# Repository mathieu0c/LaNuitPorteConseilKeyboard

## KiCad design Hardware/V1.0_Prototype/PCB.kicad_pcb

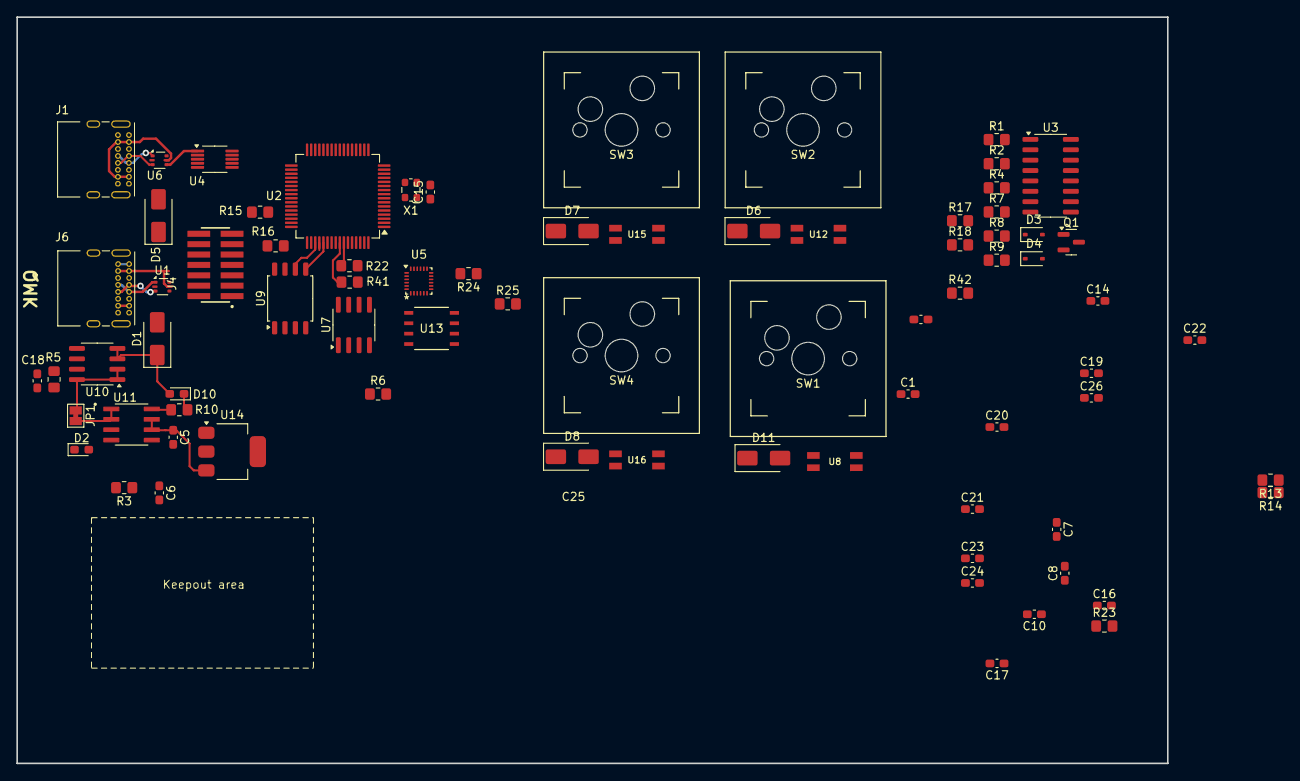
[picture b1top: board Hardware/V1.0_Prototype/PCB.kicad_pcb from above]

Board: 2 copper layers, 140.7 x 91.3 mm, 78 parts (0 on the bottom side), 72 nets.

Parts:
C1, C7, C8, C10, C14, C15, C16, C17, C20, C21, C22, C23, C24, C25: 100nF; C_0603_1608Metric_Pad1.08x0.95mm_HandSolder
C5, C6, C18: 4.7uF; C_0603_1608Metric_Pad1.08x0.95mm_HandSolder
C19, C26: 1µF; C_0603_1608Metric_Pad1.08x0.95mm_HandSolder
D1, D5: SS24; D_SMA
D2, D10: LED; LED_0603_1608Metric_Pad1.05x0.95mm_HandSolder
D3: Z3.3V; D_SOD-323
D4: BAS16HT1G; D_SOD-323
D6, D7, D8, D11: SR360; D_SMA
DS2: OLED-PCB_MOUNT_128_64_30P_Pins; SSD1306_OLED_0.96_PCB
J1, J6: USB_C_Receptacle; USB_C_Receptacle_GCT_USB4085
J4: FTSH-107-01-L-DV-K-P-TR; SAMTEC_FTSH-107-01-L-DV-K-P-TR
JP1: SolderJumper_2_Bridged; SolderJumper-2_P1.3mm_Bridged_Pad1.0x1.5mm
Q1: NMOS; SOT-23
R1: 1k; R_0805_2012Metric_Pad1.20x1.40mm_HandSolder
R2: 100; R_0805_2012Metric_Pad1.20x1.40mm_HandSolder
R3, R5, R10: 330; R_0805_2012Metric_Pad1.20x1.40mm_HandSolder
R4: 18; R_0805_2012Metric_Pad1.20x1.40mm_HandSolder
R6, R9, R23, R24, R25: 10k; R_0805_2012Metric_Pad1.20x1.40mm_HandSolder
R7, R8: 100k; R_0805_2012Metric_Pad1.20x1.40mm_HandSolder
R13, R14, R15, R16, R17, R18: 0; R_0805_2012Metric_Pad1.20x1.40mm_HandSolder
R22, R41, R42: 4.7k; R_0805_2012Metric_Pad1.20x1.40mm_HandSolder
SW1, SW2, SW3, SW4: SW_HotSwap; Hotswap_1U
U1, U6: USBLC6-2P6; SOT-666
U2: STM32F303RETx; LQFP-64_10x10mm_P0.5mm
U3: MC1413BD; SOIC-16_3.9x9.9mm_P1.27mm
U4: CH340E; MSOP-10_3x3mm_P0.5mm
U5: MPU-9250; InvenSense_QFN-24_3x3mm_P0.4mm
U7: DS3231Z; SOIC-8_3.9x4.9mm_P1.27mm
U8, U12, U15, U16: SK6812MINI-E
U9: W25Q128JVS; SOIC-8_5.3x5.3mm_P1.27mm
U10: ACS712xLCTR-05B; SOIC-8_3.9x4.9mm_P1.27mm
U11: ST890
U13: HIH6130-021-001; IC8_HIH6130-021-001_HNW
U14: AMS1117-3.3; SOT-223-3_TabPin2
X1: ECS-2520MV-250-DN-TR; Oscillator_SMD_ECS_2520MV-xxx-xx-4Pin_2.5x2.0mm

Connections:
/EEPROM/+3.3V: C17.2, U9.7 (~HOLD/~RESET/IO_{3})
/EEPROM/CLK: U2.51 (SPI3_SCK), U9.6 (CLK)
/EEPROM/GND: C17.1, U9.4 (GND)
/EEPROM/MISO: U2.52 (SPI3_MISO), U9.2 (DO/IO_{1})
/EEPROM/MOSI: U2.53 (SPI3_MOSI), U9.5 (DI/IO_{0})
/IMU/+3.3V: C6.1, C7.1, C8.1, C10.1, C14.1, C15.1, C21.1, C22.1, C23.1, C24.1, C25.1, D2.2 (A), DS2.6 (VBAT), DS2.9 (VDD), DS2.11 (BS1), DS2.28 (VCC), R24.1, U2.1 (VBAT), U2.13 (VDDA), U2.19 (VDD), U2.32 (VDD), U2.48 (VDD), U2.64 (VDD), U5.8 (VDDIO), U5.13 (VDD), U5.22 (~CS), U13.8 (Vdd), U14.2 (VO), X1.1 (Tri-State), X1.4 (VDD)
/IMU/SCL: R22.2, U2.58 (I2C1_SCL), U5.23 (SCL/SCLK), U7.8 (SCL), U13.3 (SCL)
/IMU/SDA: R41.2, U2.57 (I2C3_SDA), U5.24 (SDA/MOSI), U7.7 (SDA), U13.4 (SDA)
/Key_1U2/Led_Output: U15.P$4 (DOUT), U16.P$3 (DIN)
/Key_1U2/Row_Input: D7.1 (K), D8.1 (K)
/Key_1U/Led_Output: U8.P$4 (DOUT), U12.P$3 (DIN)
/Key_1U/Row_Input: D6.1 (K), D11.1 (K)
/MCU/NRST: J4.12, U2.7 (NRST)
/MCU/RX: U2.43 (PA10), U4.8 (TXD)
/MCU/SWC: J4.06, R16.2
/MCU/SWD: J4.04, R15.2
/MCU/TX: U2.42 (PA9), U4.9 (RXD)
/MCU/USB+: R14.2, U1.4 (I/O2)
/MCU/USB-: R13.2, U1.6 (I/O1)
/MCU/VCC_MCU: R22.1, R41.1
/Multimeter/+5V: C5.1, U11.6 (OUT), U11.7 (OUT), U14.3 (VI)
/Multimeter/ADC_OUT: D3.1 (K), D4.1 (K), Q1.3 (S), R1.2, R2.2, R4.1, R7.2, R9.2
/RTC/+3.3V: C20.2, U7.2 (VCC), U7.6 (VBAT)
/RTC/GND: C20.1, U7.5 (GND)
/Supply/+5V: D1.1 (K), D5.1 (K), D10.2 (A), U10.3 (IP-), U10.4 (IP-)
/Supply/GND: C18.2, R6.1, U10.5 (GND), U11.3 (~ON), U11.4 (GND)
/UART_Slot/DATA+: U4.1 (UD+), U6.4 (I/O2)
/UART_Slot/DATA-: U4.2 (UD-), U6.6 (I/O1)
/UART_Slot/GND: C1.2, J1.A1 (GND), J1.A12 (GND), J1.B1 (GND), J1.B12 (GND), U4.3 (GND), U6.2 (GND)
/UART_Slot/VBus: D5.2 (A), J1.A4 (VBUS), J1.A9 (VBUS), J1.B4 (VBUS), J1.B9 (VBUS), U6.5 (VBUS)
/USB_Slot/VBus: D1.2 (A), J6.A4 (VBUS), J6.A9 (VBUS), J6.B4 (VBUS), J6.B9 (VBUS), U1.5 (VBUS)
GND: C7.2, C8.2, C10.2, C14.2, C15.2, C16.2, C21.2, C22.2, C23.2, C24.2, C25.2, D3.2 (A), DS2.10 (BS0), DS2.12 (BS2), DS2.13 (~CS), J4.05, J4.07, J4.11, J6.A1 (GND), J6.A12 (GND), J6.B1 (GND), J6.B12 (GND), R17.1, R23.2, R25.1, U1.2 (GND), U2.12 (VSSA), U2.18 (VSS), U2.31 (VSS), U2.47 (VSS), U2.63 (VSS), U3.5 (I5), U3.6 (I6), U3.7 (I7), U3.8 (GND), U3.9 (COM), U5.18 (GND), U5.20 (RESV_GND), U13.2 (Vss), X1.2 (GND)
unnamed: D2.1 (K), R3.2
unnamed: D4.2 (A), R8.2
unnamed: D6.2 (A), SW2.2
unnamed: D7.2 (A), SW3.2
unnamed: D8.2 (A), SW4.2
unnamed: D10.1 (K), R10.2
unnamed: D11.2 (A), SW1.2
unnamed: C26.1, DS2.5 (C1N)
unnamed: C26.2, DS2.4 (C1P)
unnamed: C19.2, DS2.2 (C2N)
unnamed: C19.1, DS2.3 (C2P)
unnamed: DS2.1 (GND), DS2.30 (GND)
unnamed: J1.A6 (D+), J1.B6 (D+), U6.3 (I/O2)
unnamed: J1.A7 (D-), J1.B7 (D-), U6.1 (I/O1)
unnamed: J6.A6 (D+), J6.B6 (D+), U1.3 (I/O2)
unnamed: J6.A7 (D-), J6.B7 (D-), U1.1 (I/O1)
unnamed: JP1.1 (A), U10.1 (IP+), U10.2 (IP+), U10.8 (VCC)
unnamed: JP1.2 (B), U11.1 (IN), U11.2 (IN)
unnamed: Q1.1 (D), R4.2
unnamed: Q1.2 (G), R8.1
unnamed: R17.2, U2.60 (BOOT0)
unnamed: R13.1, U2.44 (USB_DM)
unnamed: R14.1, U2.45 (USB_DP)
unnamed: R15.1, U2.46 (SYS_JTMS-SWDIO)
unnamed: R16.1, U2.49 (SYS_JTCK-SWCLK)
unnamed: R42.1, U2.62 (PB9)
unnamed: R18.2, U2.5 (PF0)
unnamed: R2.1, U3.16 (O1)
unnamed: R1.1, U3.15 (O2)
unnamed: R9.1, U3.14 (O3)
unnamed: R7.1, U3.13 (O4)
unnamed: C1.1, U4.10 (V3)
unnamed: R24.2, R25.2, U5.9 (AD0/MISO)
unnamed: R23.1, U5.11 (FSYNC)
unnamed: C16.1, U5.10 (REGOUT)
unnamed: C18.1, R5.1, U10.7 (VIOUT)
unnamed: R6.2, U11.5 (SET)
unnamed: R10.1, U11.8 (~FAULT)
unnamed: C5.2, C6.2, R3.1, U14.1 (GND)
unnamed: R18.1, X1.3 (OUT)

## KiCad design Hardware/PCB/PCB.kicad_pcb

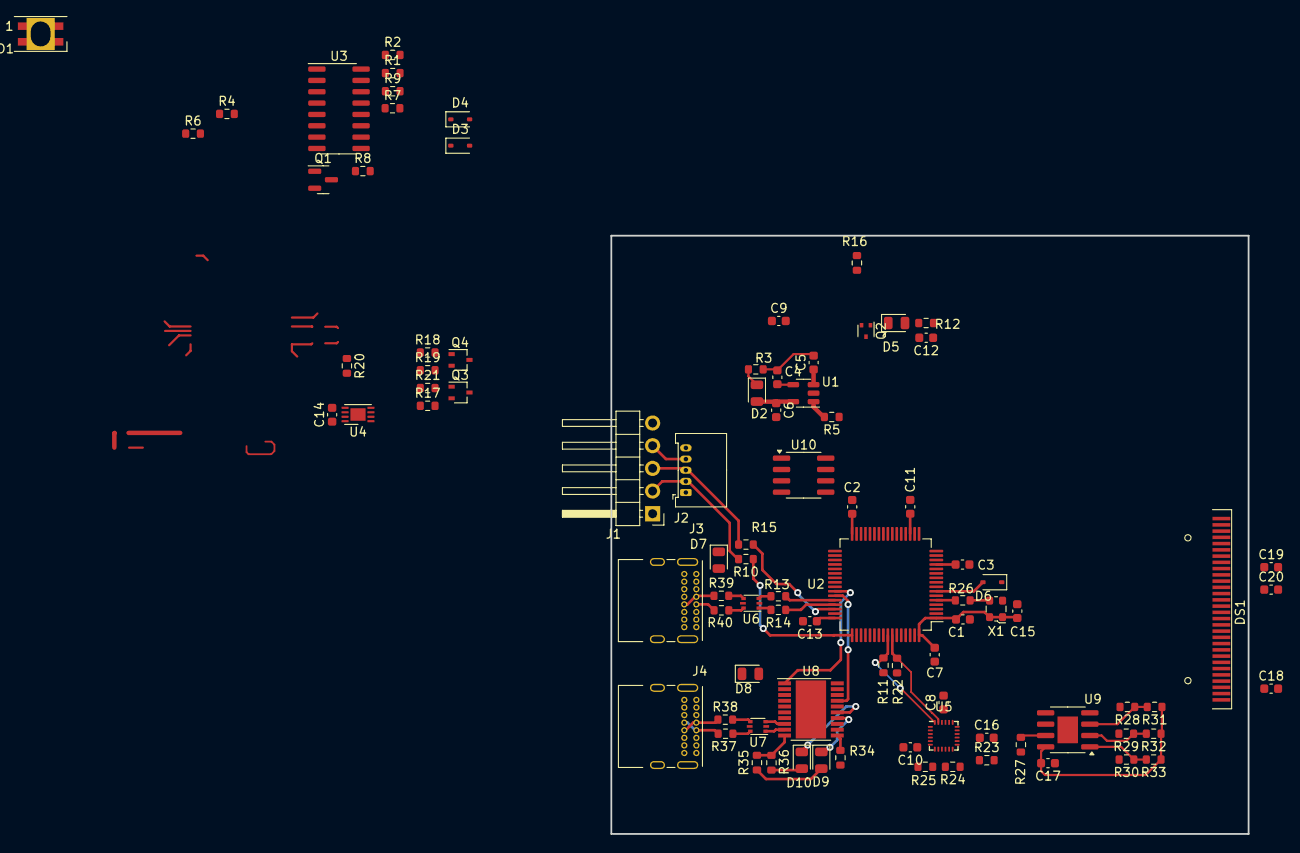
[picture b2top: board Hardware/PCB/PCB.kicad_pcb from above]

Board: 2 copper layers, 71.4 x 67.0 mm, 92 parts (1 on the bottom side), 69 nets.

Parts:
C1, C2, C3, C4, C7, C8, C9, C10, C11, C12, C13, C14, C15, C16, C17: 100nF; C_0603_1608Metric
C5, C6, C18: 4.7uF; C_0603_1608Metric
C19, C20: 1µF; C_0603_1608Metric
D1: SK6812MINI-E; LED_SK6812MINI_PLCC4_3.5x3.5mm_P1.75mm
D2, D5, D9, D10: LED; LED_0805_2012Metric
D3: Z3.3V; D_SOD-323
D4, D6: BAS16HT1G; D_SOD-323
D7, D8: D; D_0805_2012Metric
D11: SR360; D_SMA
DS1: OLED-128O064D
J1: Pin_Header; PinHeader_1x05_P2.54mm_Horizontal
J2: 53048-0510; Molex_PicoBlade_53048-0510_1x05_P1.25mm_Horizontal
J3, J4: USB_C_Receptacle_USB2.0_16P; USB_C_Receptacle_GCT_USB4085
Q1: NMOS; SOT-23
Q2: DMN33D8LT-7; SOT-523
Q3, Q4: PJC138K_R1_00001; SOT-323_SC-70
R1: 1k; R_0603_1608Metric
R2: 100; R_0603_1608Metric
R3, R5, R12, R35, R36: 270; R_0603_1608Metric
R4: 18; R_0603_1608Metric
R6, R10, R13, R14, R15: 0; R_0603_1608Metric
R7, R8, R16: 100k; R_0603_1608Metric
R9, R17, R18, R19, R21, R23, R24, R25, R27, R28, R29, R30, R31, R32, R33, R34: 10k; R_0603_1608Metric
R11, R22: 4.7k; R_0603_1608Metric
R20: 220; R_0603_1608Metric
R26: 10; R_0603_1608Metric
R37, R38, R39, R40: 22; R_0603_1608Metric
SW1: SW_HotSwap; Hotswap_1U
U1: LP2985-3.3; SOT-23-5
U2: STM32F303RETx; LQFP-64_10x10mm_P0.5mm
U3: MC1413BD; SOIC-16_3.9x9.9mm_P1.27mm
U4: MCP98243; DFN-8-1EP_3x2mm_P0.5mm_EP1.7x1.4mm
U5: MPU-9250; InvenSense_QFN-24_3x3mm_P0.4mm
U6, U7: USBLC6-2P6; SOT-666
U8: FT231XQ; HTSSOP-20-1EP_4.4x6.5mm_P0.65mm_EP3.4x6.5mm
U9: 24LC64; SOIC-8-1EP_3.9x4.9mm_P1.27mm_EP2.29x3mm
U10: ACS712xLCTR-05B; SOIC-8_3.9x4.9mm_P1.27mm
X1: ECS-2520MV-250-DN-TR; Oscillator_SMD_ECS_2520MV-xxx-xx-4Pin_2.5x2.0mm

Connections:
/EEPROM/+3.3V: C17.2, R31.1, R32.1, R33.1, U9.8 (VCC)
/EEPROM/GND: C17.1, R27.2, R28.2, R29.2, R30.2, U9.4 (GND)
/IMU/+3.3V: C1.1, C2.1, C3.1, C6.1, C7.1, C8.1, C10.1, C11.1, C13.1, C14.1, C15.1, D2.2 (A), Q3.2 (G), Q4.2 (G), R17.2, R21.2, R24.1, U1.5 (VOUT), U2.1 (VBAT), U2.13 (VDDA), U2.19 (VDD), U2.32 (VDD), U2.48 (VDD), U2.64 (VDD), U4.8 (V_{DD}), U5.8 (VDDIO), U5.13 (VDD), U5.22 (~CS), X1.1 (Tri-State), X1.4 (VDD)
/IMU/SCL: Q3.1 (D), R21.1, R22.2, U2.58 (PB6), U4.2 (SCL), U5.23 (SCL/SCLK)
/IMU/SDA: Q4.1 (D), R11.2, R17.1, U2.57 (PB5), U4.1 (SDA), U5.24 (SDA/MOSI)
/MCU/NRST: C9.1, D6.2 (A), U2.7 (NRST)
/MCU/RX: U2.43 (PA10), U8.17 (TXD)
/MCU/SWC: J1.2, J2.2, R10.2
/MCU/SWD: J1.3, J2.3, Q2.2 (G), R15.2, R16.1
/MCU/TX: U2.42 (PA9), U8.1 (RXD)
/MCU/USB+: R13.2, U6.3 (I/O2)
/MCU/USB-: R14.2, U6.1 (I/O1)
/MCU/VCC_MCU: R11.1, R22.1
/Multimeter/+5V: R18.2, R19.2, U10.3 (IP-), U10.4 (IP-)
/Multimeter/ADC_OUT: D3.1 (K), D4.1 (K), Q1.3 (S), R1.2, R2.2, R4.1, R7.2, R9.2
/OLED/LevelShifter/SCL_HL: Q3.3 (S), R18.1
/OLED/LevelShifter/SDA_HL: Q4.3 (S), R19.1
/Programming/+5V_OUT: C12.1, D7.1 (K), D8.1 (K), J1.4, J2.4, R12.1
/Supply/GND: C4.2, C5.2, C6.2, C18.2, R3.1, U1.2 (GND), U10.5 (GND)
/UART_Slot/+3.3V: R34.1, R35.1, R36.1, U8.10 (3V3OUT)
/UART_Slot/VBus: D8.2 (A), J4.A4 (VBUS), J4.A9 (VBUS), J4.B4 (VBUS), J4.B9 (VBUS), U7.5 (VBUS), U8.12 (VCC), U8.20 (VCCIO)
/USB_Slot/VBus: D7.2 (A), J3.A4 (VBUS), J3.A9 (VBUS), J3.B4 (VBUS), J3.B9 (VBUS), U6.5 (VBUS)
GND: C1.2, C2.2, C3.2, C7.2, C8.2, C9.2, C10.2, C11.2, C12.2, C13.2, C14.2, C15.2, C16.2, D3.2 (A), J1.5, J2.5, J3.A1 (GND), J3.A12 (GND), J3.B1 (GND), J3.B12 (GND), J3.S1 (SHIELD), J4.A1 (GND), J4.A12 (GND), J4.B1 (GND), J4.B12 (GND), J4.S1 (SHIELD), Q2.3 (S), R6.1, R16.2, R23.2, R25.1, U2.12 (VSSA), U2.18 (VSS), U2.31 (VSS), U2.47 (VSS), U2.63 (VSS), U3.5 (I5), U3.6 (I6), U3.7 (I7), U3.8 (GND), U3.9 (COM), U4.4 (GND), U4.5 (A2), U4.6 (A1), U4.7 (A0), U4.9 (EP/GND), U5.18 (GND), U5.20 (RESV_GND), U7.2 (GND), U8.3 (GND), U8.13 (GND), U8.21 (GND), X1.2 (GND)
unnamed: D2.1 (K), R3.2
unnamed: D4.2 (A), R8.2
unnamed: D5.2 (A), R12.2
unnamed: D5.1 (K), Q2.1 (D)
unnamed: D6.1 (K), J1.1, J2.1
unnamed: D9.2 (A), R35.2
unnamed: D9.1 (K), U8.14 (CBUS1)
unnamed: D10.2 (A), R36.2
unnamed: D10.1 (K), U8.15 (CBUS0)
unnamed: D11.2 (A), SW1.2
unnamed: DS1.1 (GND), DS1.30 (GND)
unnamed: J3.A6 (D+), J3.B6 (D+), R39.1
unnamed: J3.A7 (D-), J3.B7 (D-), R40.1
unnamed: J4.A6 (D+), J4.B6 (D+), R38.1
unnamed: J4.A7 (D-), J4.B7 (D-), R37.1
unnamed: Q1.1 (D), R4.2
unnamed: Q1.2 (G), R8.1
unnamed: R37.2, U7.6 (I/O1)
unnamed: R38.2, U7.4 (I/O2)
unnamed: R39.2, U6.4 (I/O2)
unnamed: R40.2, U6.6 (I/O1)
unnamed: C4.1, U1.4 (BP)
unnamed: C5.1, U1.1 (VIN), U1.3 (ON/~OFF), U10.1 (IP+), U10.2 (IP+), U10.8 (VCC)
unnamed: R6.2, U2.60 (BOOT0)
unnamed: R13.1, U2.44 (PA11)
unnamed: R14.1, U2.45 (PA12)
unnamed: R15.1, U2.46 (PA13)
unnamed: R10.1, U2.49 (PA14)
unnamed: R20.1, U2.62 (PB9)
unnamed: R26.2, U2.5 (PF0)
unnamed: R2.1, U3.16 (O1)
unnamed: R1.1, U3.15 (O2)
unnamed: R9.1, U3.14 (O3)
unnamed: R7.1, U3.13 (O4)
unnamed: R24.2, R25.2, U5.9 (AD0/MISO)
unnamed: R23.1, U5.11 (FSYNC)
unnamed: C16.1, U5.10 (REGOUT)
unnamed: U7.1 (I/O1), U8.9 (USBDM)
unnamed: U7.3 (I/O2), U8.8 (USBDP)
unnamed: R34.2, U8.11 (~RESET)
unnamed: R30.1, R33.2, U9.1 (A0)
unnamed: R29.1, R32.2, U9.2 (A1)
unnamed: R28.1, R31.2, U9.3 (A2)
unnamed: R27.1, U9.7 (WP)
unnamed: C18.1, R5.1, U10.7 (VIOUT)
unnamed: R26.1, X1.3 (OUT)

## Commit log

2023-05-08 Add some directories
2023-05-13 ...test...
2023-05-13 Add keyboard submodule
2023-05-13 Added layout
2023-05-13 first schematic
2023-05-13 Updated layout
2023-11-25 Update of schematic and PCB
2023-12-18 Update schematic
2024-01-27 Update of PCB and schematic
2024-07-24 update of directory
2025-01-19 save
2025-11-15 update repo, add proto PCB
